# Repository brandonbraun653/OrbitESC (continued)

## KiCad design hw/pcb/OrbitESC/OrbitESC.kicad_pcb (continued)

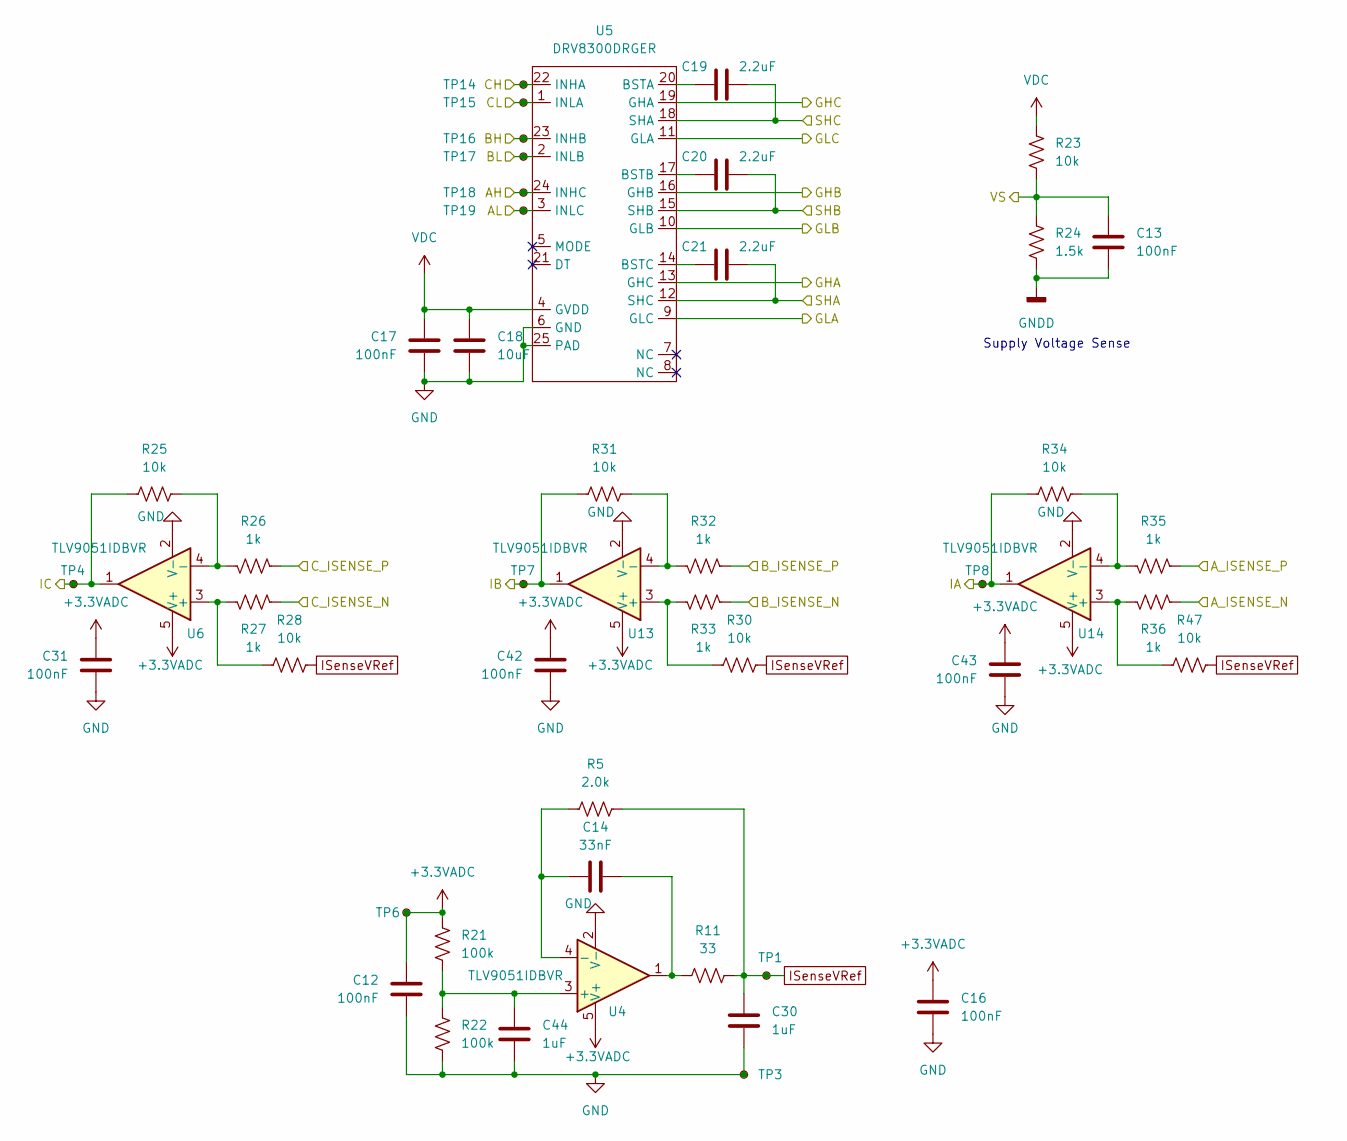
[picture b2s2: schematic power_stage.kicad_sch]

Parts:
C12, C13, C16, C17, C31, C42, C43: 100nF; C_0402_1005Metric; LCSC C307331
C14: 33nF; C_0402_1005Metric; LCSC C1585
C18: 10uF; C_0805_2012Metric; LCSC C440198
C19, C20, C21: 2.2uF; C_0805_2012Metric; LCSC C49217
C30, C44: 1uF; C_0402_1005Metric; LCSC C52923
R5: 2.0k; R_0402_1005Metric; LCSC C4109
R11: 33; R_0402_1005Metric; LCSC C25105
R21, R22: 100k; R_0402_1005Metric; LCSC C25741
R23, R25, R28, R30, R31, R34, R47: 10k; R_0402_1005Metric; LCSC C25744
R24: 1.5k; R_0402_1005Metric; LCSC C25867
R26, R27, R32, R33, R35, R36: 1k; R_0402_1005Metric; LCSC C11702
TP1, TP3, TP17: BL; TestPoint_Pad_D1.0mm
TP4, TP6, TP7, TP8, TP14: AH; TestPoint_Pad_D1.0mm
TP15: AL; TestPoint_Pad_D1.0mm
TP16: BH; TestPoint_Pad_D1.0mm
TP18: CH; TestPoint_Pad_D1.0mm
TP19: CL; TestPoint_Pad_D1.0mm
U4, U6, U13, U14: TLV9051IDBVR; SOT-23-5; LCSC C1849429
U5: DRV8300DRGER; VQFN-24-1EP_4x4mm_P0.5mm_EP2.45x2.45mm; DigiKey 296-DRV8300DRGERCT-ND

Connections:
+3.3VADC: C12.2, C16.1, C31.1, C42.1, C43.1, R21.2, TP6.1, U4.5 (V+), U6.5 (V+), U13.5 (V+), U14.5 (V+); also elsewhere on the board
/MCU/GATE_DRIVE_AH: TP18.1, U5.24 (INHC); also elsewhere on the board
/MCU/GATE_DRIVE_AL: TP19.1, U5.3 (INLC); also elsewhere on the board
/MCU/GATE_DRIVE_BH: TP16.1, U5.23 (INHB); also elsewhere on the board
/MCU/GATE_DRIVE_BL: TP17.1, U5.2 (INLB); also elsewhere on the board
/MCU/GATE_DRIVE_CH: TP14.1, U5.22 (INHA); also elsewhere on the board
/MCU/GATE_DRIVE_CL: TP15.1, U5.1 (INLA); also elsewhere on the board
/MCU/INPUT_VOLTAGE: C13.1, R23.1, R24.1; also elsewhere on the board
/MCU/MOTOR_IA: R34.1, TP8.1, U14.1; also elsewhere on the board
/MCU/MOTOR_IB: R31.1, TP7.1, U13.1; also elsewhere on the board
/MCU/MOTOR_IC: R25.1, TP4.1, U6.1; also elsewhere on the board
/Outputs and Shunts/A_ISENSE_P: R35.1; also elsewhere on the board
/Outputs and Shunts/B_ISENSE_P: R32.1; also elsewhere on the board
/Outputs and Shunts/C_ISENSE_P: R26.1; also elsewhere on the board
/Outputs and Shunts/GDH_A: U5.13 (GHC); also elsewhere on the board
/Outputs and Shunts/GDH_B: U5.16 (GHB); also elsewhere on the board
/Outputs and Shunts/GDH_C: U5.19 (GHA); also elsewhere on the board
/Outputs and Shunts/GDL_A: U5.9 (GLC); also elsewhere on the board
/Outputs and Shunts/GDL_B: U5.10 (GLB); also elsewhere on the board
/Outputs and Shunts/GDL_C: U5.11 (GLA); also elsewhere on the board
/Outputs and Shunts/SH_A: C21.2, U5.12 (SHC); also elsewhere on the board
/Outputs and Shunts/SH_B: C20.2, U5.15 (SHB); also elsewhere on the board
/Outputs and Shunts/SH_C: C19.2, U5.18 (SHA); also elsewhere on the board
GND: C12.1, C13.2, C16.2, C17.1, C18.2, C30.2, C31.2, C42.2, C43.2, C44.2, R22.1, R24.2, R27.1, R33.1, R36.1, TP3.1, U4.2 (V-), U5.6 (GND), U5.25 (PAD), U6.2 (V-), U13.2 (V-), U14.2 (V-); also elsewhere on the board
ISenseVRef: C30.1, R5.1, R11.1, R28.2, R30.2, R47.2, TP1.1
unnamed: C14.1, R5.2, U4.4 (-)
unnamed: C14.2, R11.2, U4.1
unnamed: C19.1, U5.20 (BSTA)
unnamed: C20.1, U5.17 (BSTB)
unnamed: C21.1, U5.14 (BSTC)
unnamed: C44.1, R21.1, R22.2, U4.3 (+)
unnamed: R25.2, R26.2, U6.4 (-)
unnamed: R27.2, R28.1, U6.3 (+)
unnamed: R30.1, R33.2, U13.3 (+)
unnamed: R31.2, R32.2, U13.4 (-)
unnamed: R34.2, R35.2, U14.4 (-)
unnamed: R36.2, R47.1, U14.3 (+)
VDC: C17.2, C18.1, R23.2, U5.4 (GVDD); also elsewhere on the board

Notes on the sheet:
Supply Voltage Sense

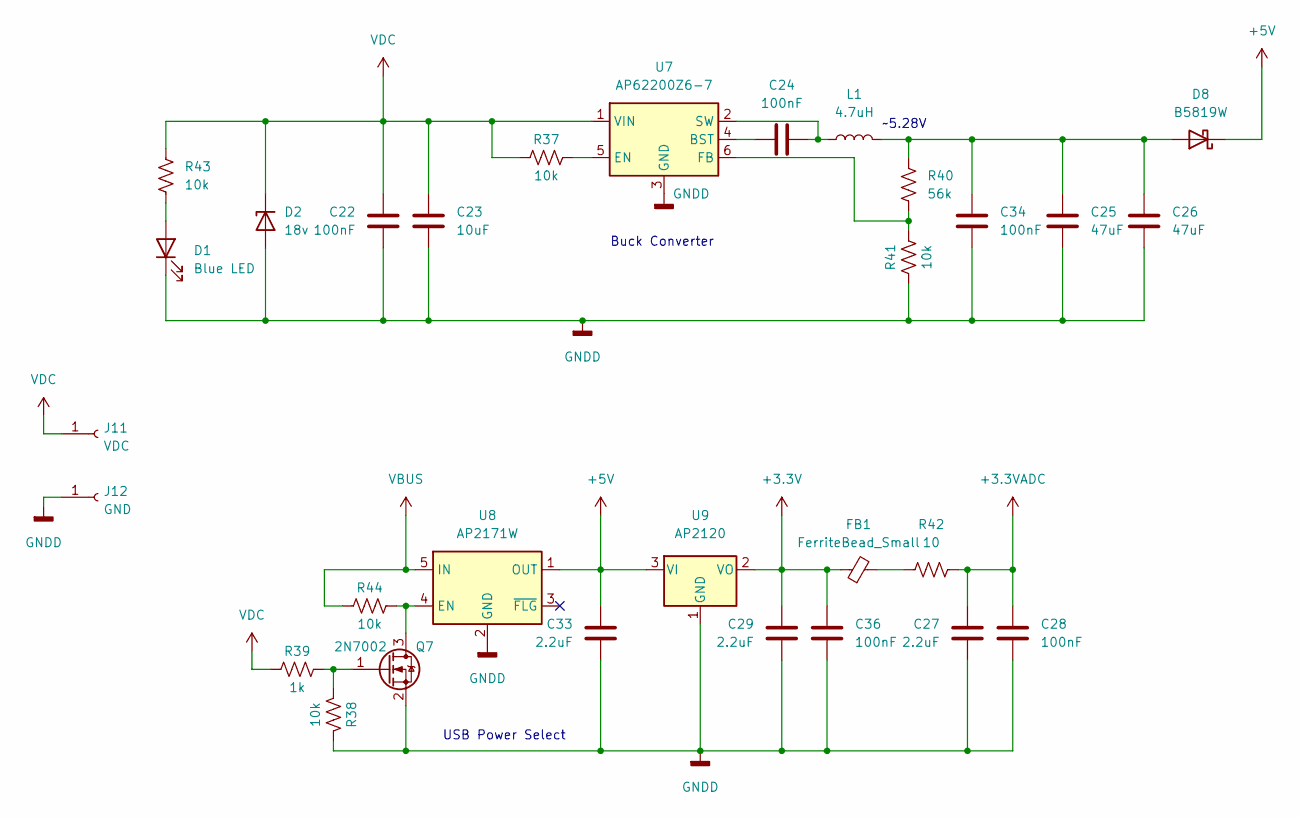
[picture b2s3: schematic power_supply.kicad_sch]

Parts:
C22, C24, C28, C34, C36: 100nF; C_0402_1005Metric; LCSC C307331
C23: 10uF; C_0805_2012Metric; LCSC C440198
C25, C26: 47uF; C_0805_2012Metric; LCSC C16780
C27, C29, C33: 2.2uF; C_0805_2012Metric; LCSC C49217
D1: Blue LED; D_0603_1608Metric; LCSC C72041
D2: 18v; D_SMA; DigiKey SMAZ18-FDICT-ND
D8: B5819W; D_SOD-123; LCSC C8598
FB1: FerriteBead_Small; R_0603_1608Metric; LCSC C1002
J11: VDC; TestPoint_Pad_4.0x4.0mm; DigiKey N/A
J12: GND; TestPoint_Pad_4.0x4.0mm; DigiKey N/A
L1: 4.7uH; L_Bourns-SRN6028; DigiKey 587-2100-1-ND
Q7: 2N7002; SOT-23; LCSC C8545
R37, R38, R41, R43, R44: 10k; R_0402_1005Metric; LCSC C25744
R39: 1k; R_0402_1005Metric; LCSC C11702
R40: 56k; R_0402_1005Metric; DigiKey RMCF0402FT57K6CT-ND
R42: 10; R_0402_1005Metric; LCSC C25077
U7: AP62200Z6-7; SOT-563; DigiKey 31-AP62200Z6-7CT-ND
U8: AP2171W; SOT-23-5; DigiKey AP2171WGDICT-ND
U9: AP2120; SOT-23; DigiKey AP2120N-3.3TRG1DICT-ND

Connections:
+3.3V: C29.2, C36.1, FB1.1, U9.2 (VO); also elsewhere on the board
+3.3VADC: C27.2, C28.1, R42.2; also elsewhere on the board
+5V: C33.2, D8.1 (K), U8.1 (OUT), U9.3 (VI); also elsewhere on the board
GND: C22.1, C23.2, C25.2, C26.2, C27.1, C28.2, C29.1, C33.1, C34.2, C36.2, D1.1 (K), D2.2 (A), J12.1, Q7.2 (S), R38.1, R41.1, U7.3 (GND), U8.2 (GND), U9.1 (GND); also elsewhere on the board
unnamed: C24.1, L1.1, U7.2 (SW)
unnamed: C24.2, U7.4 (BST)
unnamed: C25.1, C26.1, C34.1, D8.2 (A), L1.2, R40.1
unnamed: D1.2 (A), R43.2
unnamed: FB1.2, R42.1
unnamed: Q7.1 (G), R38.2, R39.2
unnamed: Q7.3 (D), R44.2, U8.4 (EN)
unnamed: R37.2, U7.5 (EN)
unnamed: R40.2, R41.2, U7.6 (FB)
VBUS: R44.1, U8.5 (IN); also elsewhere on the board
VDC: C22.2, C23.1, D2.1 (K), J11.1, R37.1, R39.1, R43.1, U7.1 (VIN); also elsewhere on the board

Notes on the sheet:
~5.28V
Buck Converter
USB Power Select

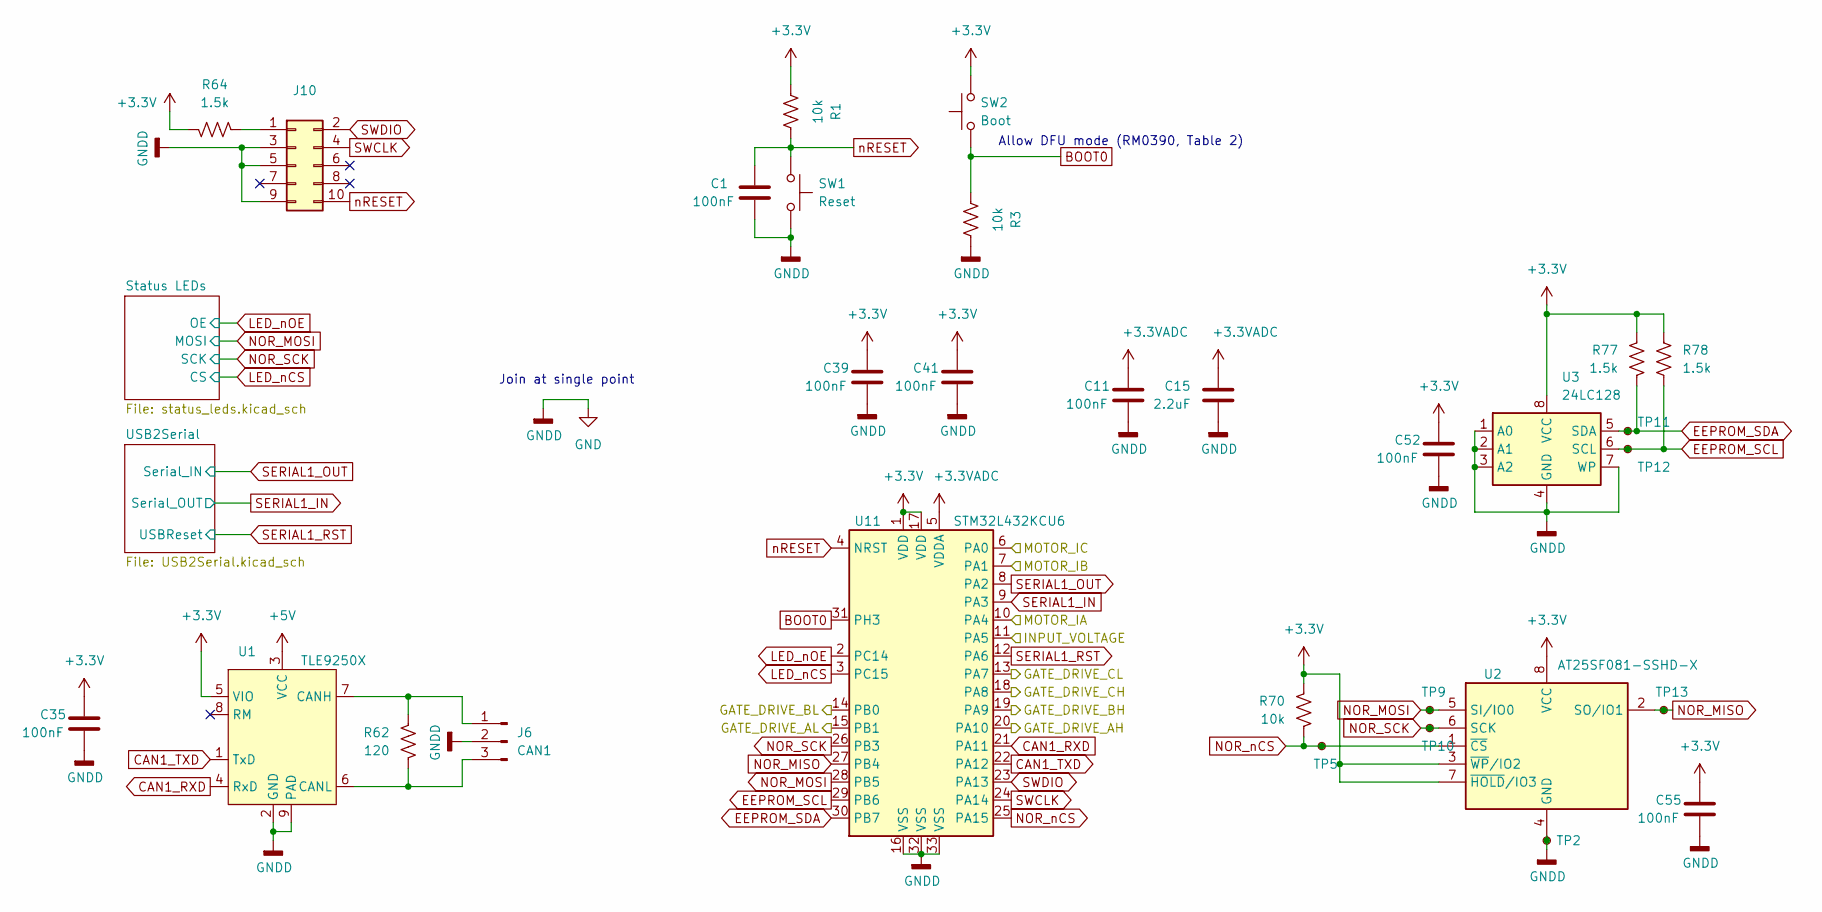
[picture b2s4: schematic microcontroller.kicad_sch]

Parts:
C1, C11, C35, C39, C41, C52, C55: 100nF; C_0402_1005Metric; LCSC C307331
C15: 2.2uF; C_0805_2012Metric; LCSC C49217
J6: CAN1; JST_PH_B3B-PH-K_1x03_P2.00mm_Vertical; DigiKey A100035-ND
J10: PinHeader_2x05_P1.27mm_Vertical; DigiKey 609-3712-ND
R1, R3, R70: 10k; R_0402_1005Metric; LCSC C25744
R62: 120; R_0402_1005Metric; LCSC C25079
R64, R77, R78: 1.5k; R_0402_1005Metric; LCSC C25867
SW1: Reset; SW_SPST_PTS810; DigiKey CKN10502CT-ND
SW2: Boot; SW_SPST_PTS810; DigiKey CKN10502CT-ND
TP2, TP13: NOR_MISO; TestPoint_Pad_D1.0mm
TP5: NOR_nCS; TestPoint_Pad_D1.0mm
TP9: NOR_MOSI; TestPoint_Pad_D1.0mm
TP10: NOR_SCK; TestPoint_Pad_D1.0mm
TP11: EEPROM_SDA; TestPoint_Pad_D1.0mm
TP12: EEPROM_SCL; TestPoint_Pad_D1.0mm
U1: TLE9250X; HVSON-8-1EP_3x3mm_P0.65mm_EP1.6x2.4mm; DigiKey 448-TLE9250XLEXUMA1CT-ND
U2: AT25SF081-SSHD-X; SOIC-8_3.9x4.9mm_P1.27mm; DigiKey 1265-AT25SF081B-SSHD-B-ND
U3: 24LC128; MSOP-8_3x3mm_P0.65mm; DigiKey 24LC128T-E/MSCT-ND
U11: STM32L432KCU6; QFN-32-1EP_5x5mm_P0.5mm_EP3.45x3.45mm; LCSC C1337280

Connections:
+3.3V: C35.2, C39.2, C41.2, C52.2, C55.2, R1.2, R64.2, R70.2, R77.2, R78.1, SW2.2, U1.5 (VIO), U2.3 (~WP/IO2), U2.7 (~HOLD/IO3), U2.8 (VCC), U3.8 (VCC), U11.1 (VDD), U11.17 (VDD); also elsewhere on the board
+3.3VADC: C11.2, C15.2, U11.5 (VDDA); also elsewhere on the board
+5V: U1.3 (VCC); also elsewhere on the board
/MCU/GATE_DRIVE_AH: U11.20 (PA10); also elsewhere on the board
/MCU/GATE_DRIVE_AL: U11.15 (PB1); also elsewhere on the board
/MCU/GATE_DRIVE_BH: U11.19 (PA9); also elsewhere on the board
/MCU/GATE_DRIVE_BL: U11.14 (PB0); also elsewhere on the board
/MCU/GATE_DRIVE_CH: U11.18 (PA8); also elsewhere on the board
/MCU/GATE_DRIVE_CL: U11.13 (PA7); also elsewhere on the board
/MCU/INPUT_VOLTAGE: U11.11 (PA5); also elsewhere on the board
/MCU/MOTOR_IA: U11.10 (PA4); also elsewhere on the board
/MCU/MOTOR_IB: U11.7 (PA1); also elsewhere on the board
/MCU/MOTOR_IC: U11.6 (PA0); also elsewhere on the board
BOOT0: R3.2, SW2.1, U11.31 (PH3)
CAN1_RXD: U1.4 (RxD), U11.21 (PA11)
CAN1_TXD: U1.1 (TxD), U11.22 (PA12)
EEPROM_SCL: R78.2, TP12.1, U3.6 (SCL), U11.29 (PB6)
EEPROM_SDA: R77.1, TP11.1, U3.5 (SDA), U11.30 (PB7)
GND: C1.1, C11.1, C15.1, C35.1, C39.1, C41.1, C52.1, C55.1, J6.2, J10.3, J10.5, J10.9, R3.1, SW1.2, TP2.1, U1.2 (GND), U1.9 (PAD), U2.4 (GND), U3.1 (A0), U3.2 (A1), U3.3 (A2), U3.4 (GND), U3.7 (WP), U11.16 (VSS), U11.32 (VSS), U11.33 (VSS); also elsewhere on the board
LED_nCS: U11.3 (PC15); also elsewhere on the board
LED_nOE: U11.2 (PC14); also elsewhere on the board
NOR_MISO: TP13.1, U2.2 (SO/IO1), U11.27 (PB4)
NOR_MOSI: TP9.1, U2.5 (SI/IO0), U11.28 (PB5); also elsewhere on the board
NOR_SCK: TP10.1, U2.6 (SCK), U11.26 (PB3); also elsewhere on the board
NOR_nCS: R70.1, TP5.1, U2.1 (~CS), U11.25 (PA15)
unnamed: J6.1, R62.2, U1.7 (CANH)
unnamed: J6.3, R62.1, U1.6 (CANL)
unnamed: J10.1, R64.1
SERIAL1_IN: U11.9 (PA3); also elsewhere on the board
SERIAL1_OUT: U11.8 (PA2); also elsewhere on the board
SERIAL1_RST: U11.12 (PA6); also elsewhere on the board
SWCLK: J10.4, U11.24 (PA14)
SWDIO: J10.2, U11.23 (PA13)
nRESET: C1.2, J10.10, R1.1, SW1.1, U11.4 (NRST)

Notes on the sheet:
Join at single point
Allow DFU mode (RM0390, Table 2)

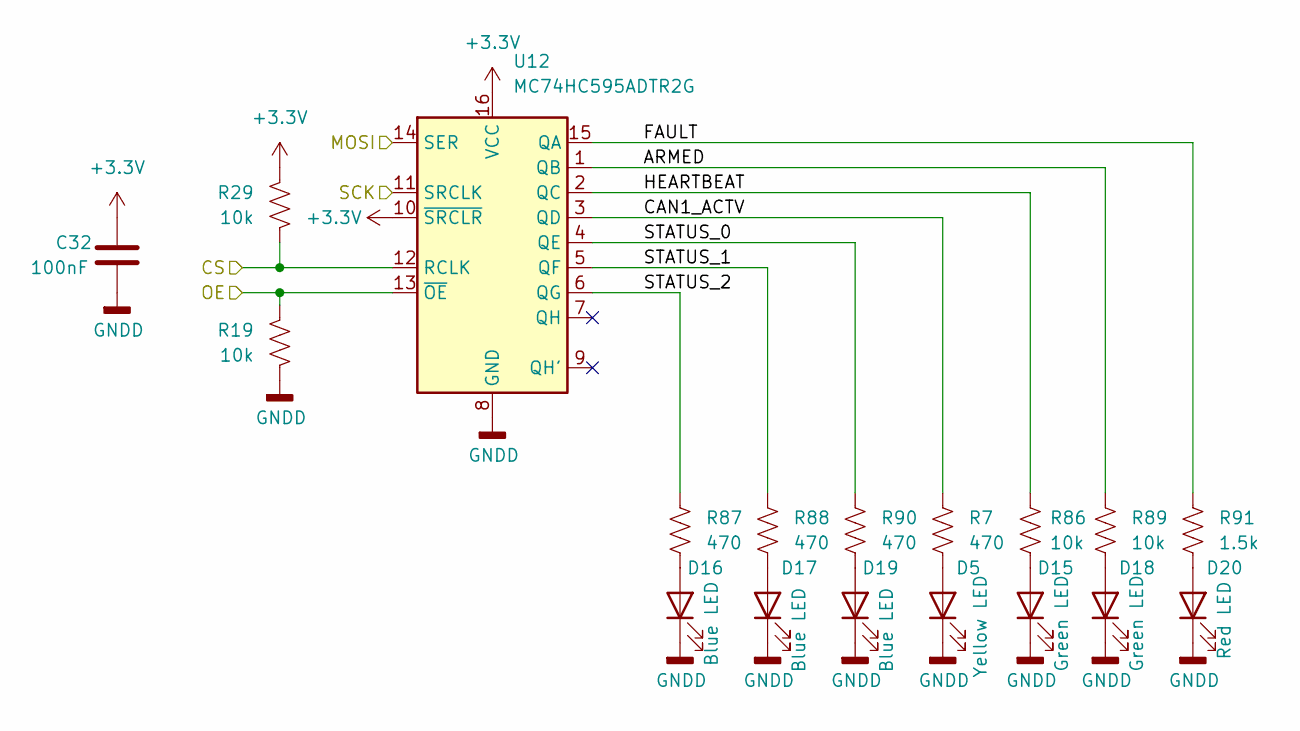
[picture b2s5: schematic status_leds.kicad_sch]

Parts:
C32: 100nF; C_0402_1005Metric; LCSC C307331
D5: Yellow LED; D_0603_1608Metric; LCSC C72038
D15, D18: Green LED; D_0603_1608Metric; LCSC C72043
D16, D17, D19: Blue LED; D_0603_1608Metric; LCSC C72041
D20: Red LED; D_0603_1608Metric; LCSC C2286
R7, R87, R88, R90: 470; R_0402_1005Metric; LCSC C25117
R19, R29, R86, R89: 10k; R_0402_1005Metric; LCSC C25744
R91: 1.5k; R_0402_1005Metric; LCSC C25867
U12: MC74HC595ADTR2G; TSSOP-16_4.4x5mm_P0.65mm; LCSC C100027

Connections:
+3.3V: C32.2, R29.2, U12.10 (~SRCLR), U12.16 (VCC); also elsewhere on the board
/MCU/Status LEDs/ARMED: R89.1, U12.1 (QB)
/MCU/Status LEDs/CAN1_ACTV: R7.1, U12.3 (QD)
/MCU/Status LEDs/FAULT: R91.1, U12.15 (QA)
/MCU/Status LEDs/HEARTBEAT: R86.1, U12.2 (QC)
/MCU/Status LEDs/STATUS_0: R90.1, U12.4 (QE)
/MCU/Status LEDs/STATUS_1: R88.1, U12.5 (QF)
/MCU/Status LEDs/STATUS_2: R87.1, U12.6 (QG)
GND: C32.1, D5.1 (K), D15.1 (K), D16.1 (K), D17.1 (K), D18.1 (K), D19.1 (K), D20.1 (K), R19.1, U12.8 (GND); also elsewhere on the board
LED_nCS: R29.1, U12.12 (RCLK); also elsewhere on the board
LED_nOE: R19.2, U12.13 (~OE); also elsewhere on the board
NOR_MOSI: U12.14 (SER); also elsewhere on the board
NOR_SCK: U12.11 (SRCLK); also elsewhere on the board
unnamed: D5.2 (A), R7.2
unnamed: D15.2 (A), R86.2
unnamed: D16.2 (A), R87.2
unnamed: D17.2 (A), R88.2
unnamed: D18.2 (A), R89.2
unnamed: D19.2 (A), R90.2
unnamed: D20.2 (A), R91.2

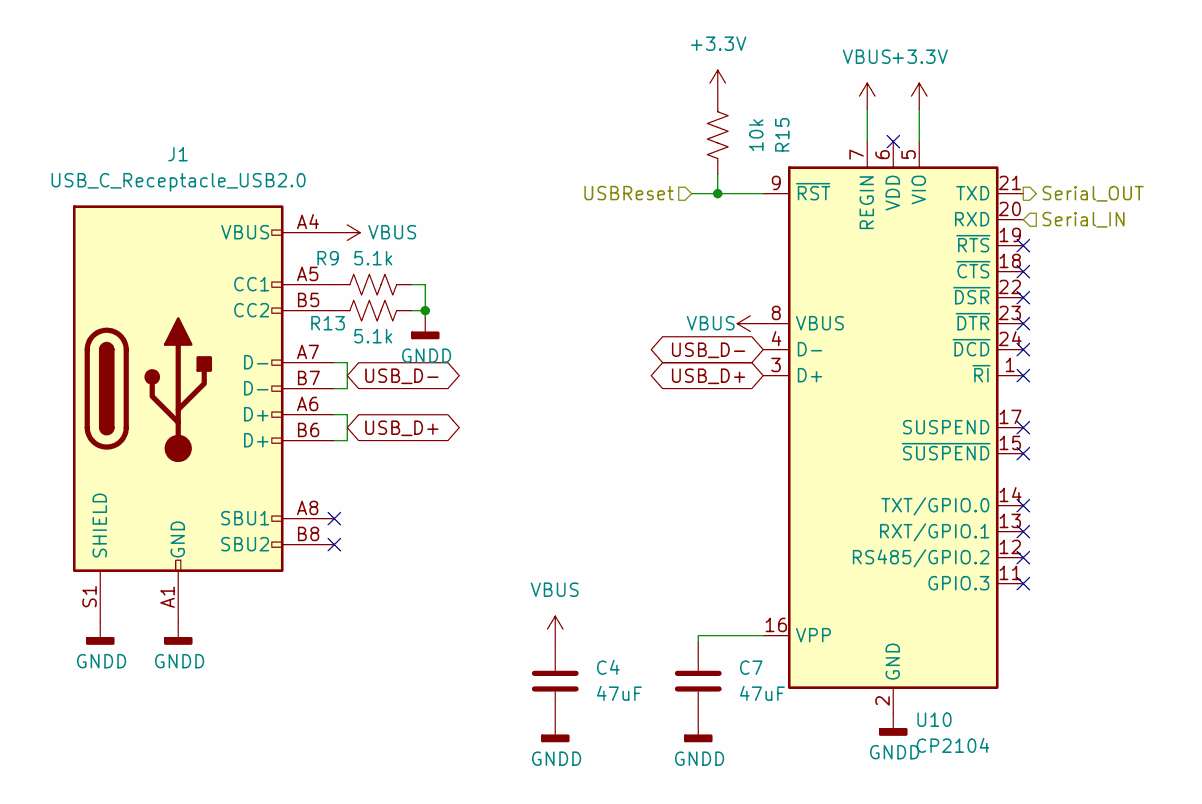
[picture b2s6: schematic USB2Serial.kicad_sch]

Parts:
C4, C7: 47uF; C_0805_2012Metric; LCSC C16780
J1: USB_C_Receptacle_USB2.0; USB_C_Receptacle_GCT_USB4085
R9, R13: 5.1k; R_0402_1005Metric; LCSC C25905
R15: 10k; R_0402_1005Metric; LCSC C25744
U10: CP2104; QFN-24-1EP_4x4mm_P0.5mm_EP2.6x2.6mm

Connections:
+3.3V: R15.2, U10.5 (VIO); also elsewhere on the board
GND: C4.2, C7.2, J1.A1 (GND), J1.A12 (GND), J1.B1 (GND), J1.B12 (GND), J1.S1 (SHIELD), R9.1, R13.2, U10.2 (GND), U10.25 (GND); also elsewhere on the board
unnamed: C7.1, U10.16 (VPP)
unnamed: J1.A5 (CC1), R9.2
unnamed: J1.B5 (CC2), R13.1
SERIAL1_IN: U10.21 (TXD); also elsewhere on the board
SERIAL1_OUT: U10.20 (RXD); also elsewhere on the board
SERIAL1_RST: R15.1, U10.9 (~RST); also elsewhere on the board
USB_D+: J1.A6 (D+), J1.B6 (D+), U10.3 (D+)
USB_D-: J1.A7 (D-), J1.B7 (D-), U10.4 (D-)
VBUS: C4.1, J1.A4 (VBUS), J1.A9 (VBUS), J1.B4 (VBUS), J1.B9 (VBUS), U10.7 (REGIN), U10.8 (VBUS); also elsewhere on the board

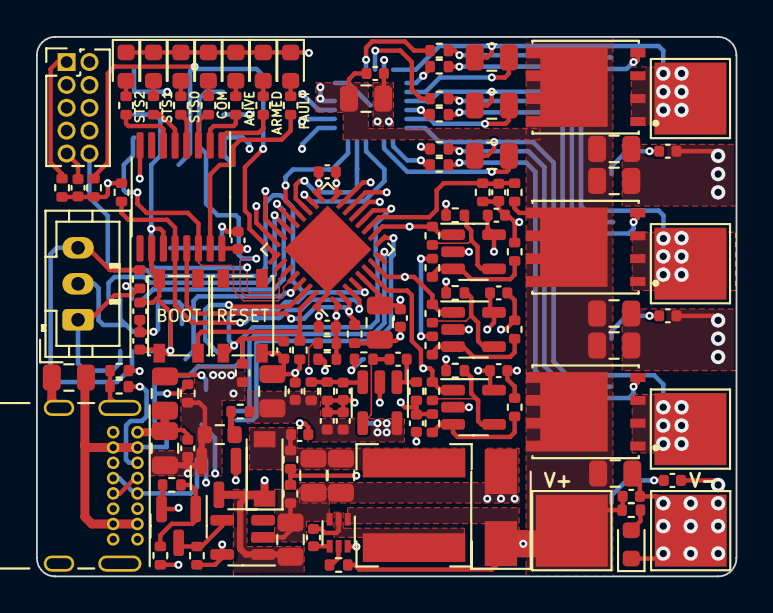
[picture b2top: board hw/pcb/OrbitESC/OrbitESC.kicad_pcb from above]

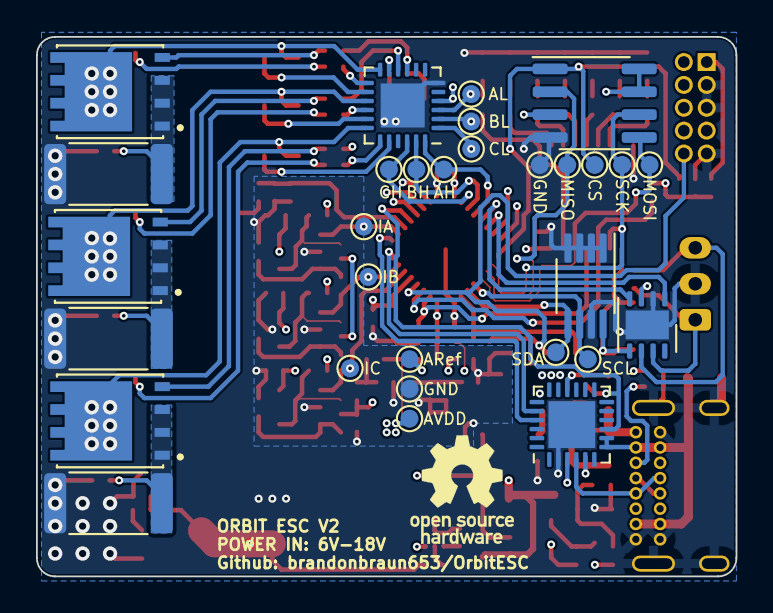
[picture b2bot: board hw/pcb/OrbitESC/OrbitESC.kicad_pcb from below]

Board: 4 copper layers, 38.9 x 30.0 mm, 159 parts (30 on the bottom side), 95 nets.

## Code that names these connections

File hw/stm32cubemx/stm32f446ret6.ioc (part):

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Mcu.Name=STM32F446R(C-E)Tx
Mcu.Package=LQFP64
Mcu.UserName=STM32F446RETx
PA0-WKUP.Signal=ADCx_IN0
PA1.Signal=ADCx_IN1
PA10.Signal=S_TIM1_CH3
PA11.Mode=CAN_Activate
PA11.Signal=CAN1_RX
PA12.Mode=CAN_Activate
PA12.Signal=CAN1_TX
PA13.Mode=Serial_Wire
PA13.Signal=SYS_JTMS-SWDIO
PA14.Mode=Serial_Wire
PA14.Signal=SYS_JTCK-SWCLK
PA15.Mode=NSS_Signal_Hard_Output
PA15.Signal=SPI1_NSS
PA2.Signal=ADCx_IN2
PA3.Signal=ADCx_IN3
PA4.Signal=ADCx_IN4
PA5.Signal=ADCx_IN5
PA7.Mode=Output Compare1 CH1 CH1N
PA7.Signal=TIM1_CH1N
PA8.Signal=S_TIM1_CH1
PA9.Signal=S_TIM1_CH2
PB0.Mode=Output Compare2 CH2 CH2N
PB0.Signal=TIM1_CH2N
PB1.Mode=Output Compare3 CH3 CH3N
PB1.Signal=TIM1_CH3N
PB10.GPIOParameters=GPIO_Label
PB10.GPIO_Label=SDIO_DET
PB10.Signal=GPIO_Input
PB12.GPIOParameters=GPIO_Label
PB12.GPIO_Label=USB_OTG_HS_RESET
PB12.Signal=GPIO_Output
PB13.Mode=Activate_VBUS_FS
PB13.Signal=USB_OTG_HS_VBUS
PB14.Mode=Device_Only_FS
PB14.Signal=USB_OTG_HS_DM
PB15.Mode=Device_Only_FS
PB15.Signal=USB_OTG_HS_DP
PB3.Mode=Full_Duplex_Master
PB3.Signal=SPI1_SCK
PB4.Mode=Full_Duplex_Master
PB4.Signal=SPI1_MISO
PB5.Mode=Full_Duplex_Master
PB5.Signal=SPI1_MOSI
PB6.GPIOParameters=GPIO_Label
PB6.GPIO_Label=Fault
PB6.Signal=GPIO_Output
PB7.GPIOParameters=GPIO_Label
PB7.GPIO_Label=Armed
PB7.Signal=GPIO_Output
PB8.GPIOParameters=GPIO_Label
PB8.GPIO_Label=Heartbeat
PB8.Signal=GPIO_Output
PB9.GPIOParameters=GPIO_Label
PB9.GPIO_Label=CAN Activity
PB9.Signal=GPIO_Output
PC0.Signal=ADCx_IN10
PC1.Signal=ADCx_IN11
PC10.Mode=SD_4_bits_Wide_bus
PC10.Signal=SDIO_D2
PC11.Mode=SD_4_bits_Wide_bus
PC11.Signal=SDIO_D3
PC12.Mode=SD_4_bits_Wide_bus
PC12.Signal=SDIO_CK
PC13.GPIOParameters=GPIO_Label
PC13.GPIO_Label=USB Activity
PC13.Signal=GPIO_Output
PC2.Signal=ADCx_IN12
PC3.Signal=ADCx_IN13
PC6.Mode=Asynchronous
PC6.Signal=USART6_TX
PC7.Mode=Asynchronous
PC7.Signal=USART6_RX
PC8.Mode=SD_4_bits_Wide_bus
PC8.Signal=SDIO_D0
PC9.Mode=SD_4_bits_Wide_bus
PC9.Signal=SDIO_D1
PD2.Mode=SD_4_bits_Wide_bus
PD2.Signal=SDIO_CMD
PH0-OSC_IN.Mode=HSE-External-Oscillator
PH0-OSC_IN.Signal=RCC_OSC_IN
PH1-OSC_OUT.Mode=HSE-External-Oscillator
PH1-OSC_OUT.Signal=RCC_OSC_OUT
RCC.HSE_VALUE=24000000
RCC.SYSCLKFreq_VALUE=180000000
RCC.SYSCLKSource=RCC_SYSCLKSOURCE_PLLCLK
board=custom

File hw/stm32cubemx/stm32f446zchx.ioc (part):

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Mcu.Name=STM32F446Z(C-E)Hx
Mcu.Package=UFBGA144
Mcu.UserName=STM32F446ZCHx
PA0-WKUP.GPIOParameters=GPIO_Label
PA0-WKUP.GPIO_Label=INPUT_VOLTAGE
PA0-WKUP.Signal=ADCx_IN0
PA1.GPIOParameters=GPIO_Label
PA1.GPIO_Label=MOTOR_IA
PA1.Signal=ADCx_IN1
PA10.GPIOParameters=GPIO_Label
PA10.GPIO_Label=USB COM LED
PA10.Signal=GPIO_Output
PA11.Mode=Device_Only
PA11.Signal=USB_OTG_FS_DM
PA12.Mode=Device_Only
PA12.Signal=USB_OTG_FS_DP
PA13.Mode=JTAG_5_pins
PA13.Signal=SYS_JTMS-SWDIO
PA14.Mode=JTAG_5_pins
PA14.Signal=SYS_JTCK-SWCLK
PA15.Mode=JTAG_5_pins
PA15.Signal=SYS_JTDI
PA2.GPIOParameters=GPIO_Label
PA2.GPIO_Label=MOTOR_IB
PA2.Signal=ADCx_IN2
PA3.GPIOParameters=GPIO_Label
PA3.GPIO_Label=MOTOR_IC
PA3.Signal=ADCx_IN3
PA4.GPIOParameters=GPIO_Label
PA4.GPIO_Label=MOTOR_VA
PA4.Signal=ADCx_IN4
PA5.GPIOParameters=GPIO_Label
PA5.GPIO_Label=MOTOR_VB
PA5.Signal=ADCx_IN5
PA6.GPIOParameters=GPIO_Label
PA6.GPIO_Label=MOTOR_VC
PA6.Signal=ADCx_IN6
PA8.GPIOParameters=GPIO_Label
PA8.GPIO_Label=USB Renumerate
PA8.Signal=GPIO_Output
PA9.Mode=Activate_VBUS
PA9.Signal=USB_OTG_FS_VBUS
PB12.GPIOParameters=GPIO_Label
PB12.GPIO_Label=SPI CS
PB12.Signal=GPIO_Output
PB13.Mode=Full_Duplex_Master
PB13.Signal=SPI2_SCK
PB14.Mode=Full_Duplex_Master
PB14.Signal=SPI2_MISO
PB15.Mode=Full_Duplex_Master
PB15.Signal=SPI2_MOSI
PB2.GPIOParameters=GPIO_Label
PB2.GPIO_Label=BOOT
PB2.Signal=GPIO_Input
PB3.Mode=JTAG_5_pins
PB3.Signal=SYS_JTDO-SWO
PB4.Mode=JTAG_5_pins
PB4.Signal=SYS_JTRST
PB5.Mode=CAN_Activate
PB5.Signal=CAN2_RX
PB6.Mode=CAN_Activate
PB6.Signal=CAN2_TX
PB8.Mode=CAN_Activate
PB8.Signal=CAN1_RX
PB9.Mode=CAN_Activate
PB9.Signal=CAN1_TX
PC0.GPIOParameters=GPIO_Label
PC0.GPIO_Label=SUPPLY_5V0
PC0.Signal=ADCx_IN10
PC10.Mode=SD_4_bits_Wide_bus
PC10.Signal=SDIO_D2
PC11.Mode=SD_4_bits_Wide_bus
PC11.Signal=SDIO_D3
PC12.Mode=SD_4_bits_Wide_bus
PC12.Signal=SDIO_CK
PC13.GPIOParameters=GPIO_Label
PC13.GPIO_Label=HEARTBEAT LED
PC13.Signal=GPIO_Output
PC8.Mode=SD_4_bits_Wide_bus
PC8.Signal=SDIO_D0
PC9.Mode=SD_4_bits_Wide_bus
PC9.Signal=SDIO_D1
PD1.GPIOParameters=GPIO_Label
PD1.GPIO_Label=SDIO_CARD_DETECT
PD1.Signal=GPXTI1
PD2.Mode=SD_4_bits_Wide_bus
PD2.Signal=SDIO_CMD
PD5.Mode=Asynchronous
PD5.Signal=USART2_TX
PD6.Mode=Asynchronous
PD6.Signal=USART2_RX
PE0.GPIOParameters=GPIO_Label
PE0.GPIO_Label=CAN1 COM LED
PE0.Signal=GPIO_Output
PE1.GPIOParameters=GPIO_Label
PE1.GPIO_Label=MOTOR_ARMED
PE1.Signal=GPIO_Output
PE10.Mode=Output Compare2 CH2 CH2N
PE10.Signal=TIM1_CH2N
PE11.Signal=S_TIM1_CH2
PE12.Mode=Output Compare3 CH3 CH3N
PE12.Signal=TIM1_CH3N
PE13.Signal=S_TIM1_CH3
PE15.GPIOParameters=GPIO_Label
PE15.GPIO_Label=BREAK
PE15.Mode=Activate-Break-Input
PE15.Signal=TIM1_BKIN
PE2.GPIOParameters=GPIO_Label
PE2.GPIO_Label=MOTOR_FAULT
PE2.Signal=GPIO_Output
PE3.GPIOParameters=GPIO_Label
PE3.GPIO_Label=USER_BTN
PE3.Signal=GPIO_Input
PE4.GPIOParameters=GPIO_Label
PE4.GPIO_Label=STATUS_0_LED
PE4.Signal=GPIO_Output
PE5.GPIOParameters=GPIO_Label
PE5.GPIO_Label=STATUS_1_LED
PE5.Signal=GPIO_Output
PE6.GPIOParameters=GPIO_Label
PE6.GPIO_Label=STATUS_2_LED
PE6.Signal=GPIO_Output
PE8.Mode=Output Compare1 CH1 CH1N
PE8.Signal=TIM1_CH1N
PE9.Signal=S_TIM1_CH1
PF0.Mode=I2C
PF0.Signal=I2C2_SDA
PF1.Mode=I2C
PF1.Signal=I2C2_SCL
PF10.GPIOParameters=GPIO_Label
PF10.GPIO_Label=SUPPLY_3V3
PF10.Mode=IN8
PF10.Signal=ADC3_IN8
PF3.GPIOParameters=GPIO_Label
PF3.GPIO_Label=BOARD_TEMP_A
PF3.Mode=IN9
PF3.Signal=ADC3_IN9
PF9.GPIOParameters=GPIO_Label
PF9.GPIO_Label=BOARD_TEMP_B
PF9.Mode=IN7
PF9.Signal=ADC3_IN7
PG12.GPIOParameters=GPIO_Label
PG12.GPIO_Label=SERIAL1_COM_LED
PG12.Signal=GPIO_Output
PG13.GPIOParameters=GPIO_Label
PG13.GPIO_Label=SERIAL2_COM_LED
PG13.Signal=GPIO_Output
PG14.Mode=Asynchronous
PG14.Signal=USART6_TX
PG15.GPIOParameters=GPIO_Label
PG15.GPIO_Label=CAN2 COM LED
PG15.Signal=GPIO_Output
PG9.Mode=Asynchronous
PG9.Signal=USART6_RX
PH0-OSC_IN.Mode=HSE-External-Oscillator
PH0-OSC_IN.Signal=RCC_OSC_IN
PH1-OSC_OUT.Mode=HSE-External-Oscillator
PH1-OSC_OUT.Signal=RCC_OSC_OUT
RCC.HSE_VALUE=24000000
RCC.SYSCLKFreq_VALUE=180000000
RCC.SYSCLKSource=RCC_SYSCLKSOURCE_PLLCLK
board=custom

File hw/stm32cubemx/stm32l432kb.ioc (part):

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Mcu.Name=STM32L432K(B-C)Ux
Mcu.Package=UFQFPN32
Mcu.UserName=STM32L432KBUx
PA0.Signal=ADCx_IN5
PA1.Signal=ADCx_IN6
PA10.Signal=S_TIM1_CH3
PA11.Mode=CAN_Activate
PA11.Signal=CAN1_RX
PA12.Mode=CAN_Activate
PA12.Signal=CAN1_TX
PA13\ (JTMS-SWDIO).Signal=SYS_JTMS-SWDIO
PA14\ (JTCK-SWCLK).Signal=SYS_JTCK-SWCLK
PA15\ (JTDI).GPIOParameters=GPIO_Label
PA15\ (JTDI).GPIO_Label=NOR_nCS
PA15\ (JTDI).Signal=GPIO_Output
PA2.Signal=ADCx_IN7
PA3.Signal=ADCx_IN8
PA4.Signal=ADCx_IN9
PA5.Signal=ADCx_IN10
PA6.Signal=ADCx_IN11
PA7.Mode=PWM Generation1 CH1 CH1N
PA7.Signal=TIM1_CH1N
PA8.Signal=S_TIM1_CH1
PA9.Signal=S_TIM1_CH2
PB0.Mode=PWM Generation2 CH2 CH2N
PB0.Signal=TIM1_CH2N
PB1.Mode=PWM Generation3 CH3 CH3N
PB1.Signal=TIM1_CH3N
PB3\ (JTDO-TRACESWO).Mode=Full_Duplex_Master
PB3\ (JTDO-TRACESWO).Signal=SPI3_SCK
PB4\ (NJTRST).Mode=Full_Duplex_Master
PB4\ (NJTRST).Signal=SPI3_MISO
PB5.Mode=Full_Duplex_Master
PB5.Signal=SPI3_MOSI
PB6.Mode=Asynchronous
PB6.Signal=USART1_TX
PB7.Mode=Asynchronous
PB7.Signal=USART1_RX
PC14-OSC32_IN\ (PC14).GPIOParameters=GPIO_Label
PC14-OSC32_IN\ (PC14).GPIO_Label=LED_nOE
PC14-OSC32_IN\ (PC14).Signal=GPIO_Output
PC15-OSC32_OUT\ (PC15).GPIOParameters=GPIO_Label
PC15-OSC32_OUT\ (PC15).GPIO_Label=LED_nCS
PC15-OSC32_OUT\ (PC15).Signal=GPIO_Output
PH3-BOOT0.GPIOParameters=GPIO_Label
PH3-BOOT0.GPIO_Label=BootMode
PH3-BOOT0.Signal=GPIO_Input
RCC.HSE_VALUE=8000000
RCC.SYSCLKFreq_VALUE=80000000
RCC.SYSCLKSource=RCC_SYSCLKSOURCE_PLLCLK
board=custom

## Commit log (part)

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2022-10-03 Sync some thoughts on how to structure the new ISR update routines
2022-10-16 Save a few board changes found when assembing PCB v1.0
2022-10-17 Save work for lunch efforts tomorrow. EEPROM updates
2022-10-17 Work on containerization
2022-10-17 Fix EEPROM addressing issues
2022-10-20 Clean up toolchain
2022-10-24 Start integration of filesystem
2022-10-26 Add placeholders for logging sinks
2022-10-26 Start adding the logging infrastructure
2022-10-28 Fill out more of the logging subsystem
2022-10-30 Filesystem mounting with no malloc
2022-10-31 Improve NOR driver
2022-11-02 Start adding some of the eeprom readout
2022-11-06 Attempts to figure out why LittleFS isn't working
2022-11-07 Get the simulator target compiling
2022-11-09 Update sim repo
2022-11-10 Try out filesystem with simulator
2022-11-11 Try out the hw build. FS doesn't seem to work.
2022-11-14 Sync for work
2022-11-16 Found bug, save work
2022-11-18 Little bit of project cleanup
2022-11-21 Start adding the system analog monitors
2022-11-24 Publish phase C current measurements
2022-11-25 Start adding simulation for analog
2022-11-26 Start integration of protocol buffers for serial command and control
2022-11-28 Add basic outline of inner control loop
2022-11-28 Schematic corrections
2022-11-29 Sync PCB updates
2022-11-30 Sync work
2022-12-01 Sync today's work
2022-12-03 Route analogs and starting power stage
2022-12-04 Route power stage of the motor drive
2022-12-06 Add FIR filter algorithm
2022-12-06 Fix some PWM issues
2022-12-08 Start refactoring FOC
2022-12-10 Implement HW analog watchdog monitoring for current and voltage
2022-12-11 Sync work for in-progress serial driver updates
2022-12-12 Increase serial buffer size to print all characters
2022-12-13 Pull up submodules
2022-12-13 Start working on proto interface
2022-12-16 Work on serial driver interface
2022-12-17 Start adding cobs framing
2022-12-20 Update kicad libs
2022-12-21 Sync between pc
2022-12-22 Sync for PC
2023-01-11 Update compiler path. Disable motor drive output enable.
2023-01-13 Sync
2023-01-17 Trying to figure out USART RX
2023-01-18 USART DMA TX working
2023-01-19 Reduce project memory usage
2023-01-22 Ping message working
2023-01-22 Update memory allocations
2023-01-24 Improve framing technique. Fix infinite loop in serial dispatcher.
2023-01-30 Increase debug port baud rate to 2MBit
2023-01-30 Sync work from lunch
2023-02-01 Start added parameter io processing
2023-02-03 Implement full parameter load/store RPC calls
2023-02-03 Parameter GET working
2023-02-05 Add improved support to parameters. Implement read-only tests
2023-02-05 Add system reset command
2023-02-06 Change LED blink rate
2023-02-28 Add mode switching tests
2023-02-28 Save lunchtime work. Change CAN bus activity LED control method.
2023-03-01 Start adding CAN id parameter setting. Freezing somewhere.
2023-03-01 Don't set CAN id to PC in test
2023-03-02 Add parameter validation on save
2023-03-06 Improve parameter storage.
2023-03-07 Add sanity tests for remaining parameters
2023-03-10 Sync some work
2023-03-14 Reorder boot initialization so peripherals can use reconfigurable settings
2023-03-18 Improve adc calibration. Maybe
2023-03-29 Validate my ISRs are firing in the new configuration
2023-03-29 Start planning out basic motor startup
2023-03-30 Sketch out startup equation
2023-03-31 Trying to figure out a decent startup routine
2023-04-11 Try and figure out current sense issues
2023-04-16 Start live plotting motor current to help with debugging ADC settings
2023-04-19 Start work on PCB v3
2023-04-24 Toy around with the driver. Start adding Qt gui
2023-04-24 Cleanup sim directory
2023-05-01 Start adding graphical interface
2023-05-04 Think I improved the current loop controller?
2023-05-06 Dramatically improve look of GUI
2023-05-08 Hurrah! I actually got closed loop current control to semi-work!
2023-05-08 Start adding GUI parameter updater
2023-05-11 Got a single parameter to update through GUI
2023-05-27 Lazy sync for work over the past few weeks. Been busy
2023-06-06 Save some PCB work
2023-06-08 Update SDIO card detect
2023-06-09 Semi-final schematic for F4 variant
2023-06-09 Save tonight's PCB work
2023-06-11 Finish initial draft of V3 pcb
2023-06-13 PCB cleanup. BOM checks.
2023-06-14 Squash feature/sync_current_ctrl/r0
2023-06-21 Update Thor
2023-06-22 Sync before branch for new board mapping
2023-06-25 Clean up a few more interfaces. Discovered NOR isn't working
2023-06-26 More board turn on things
2023-06-27 Fix USART init bug
2023-06-29 Fix NOR flash bootup
2023-08-17 Pull up submodules to include sdio driver support
2023-08-18 Pull up tinyusb to v0.15.0
2023-08-19 Update some submodule pointers.
2023-08-19 Add submodule checkout script
2023-08-20 Sync to PC
2023-08-20 Update history depth
2023-08-20 Start refactoring motor hw driver for timer split
2023-08-22 Slave timer config first attempt. Not great.
2023-08-23 Get both instrumentation and motor sense ADCs firing off timers with DMA
2023-08-26 Get debug pin toggling on ADC output
2023-08-26 Start implementing the motor control loops. Fix timer clocking issue.
2023-08-26 Formalize the debug/release build targets
2023-08-27 Update clocking scheme in MXCube
2023-08-28 Add simple motor ADC DC offset calibration
2023-09-01 Add some filtering, maybe.
2023-09-01 Update simulation
2023-09-03 Got first cut of SVM working on the controller
2023-09-04 Refactor observer methods and state publishing methods
2023-09-07 Sync initial effort to figuring out some current control parameters
2023-09-14 Remove tinyusb as a submodule
2023-09-14 Add back tinyusb from source
2023-09-14 Update the tinyusb config with possibly OK settings
2023-09-16 Remove some unused tinyusb code
2023-09-19 USB is attempting to enumerate. Not quite working yet.
2023-09-21 Remove FlashDB as submodule. Hardcoded config file.
2023-09-21 Add basic compiling of FlashDB + filesystem stubs
2023-09-28 Do a fair amount of refactoring
2023-09-29 Start connecting volatile parameter updates to persistent backing.
2023-09-30 Sync for move to new PC
2023-09-30 FAL init and writes appear to be working
2023-09-30 Finish the database backend refactor
2023-10-02 Start the transition to FatFs support for SD card
2023-10-08 First successful mounting of SD card
2023-10-08 Almost working async SD card mount/unmount
2023-10-10 Improve the file log sink
2023-10-13 Try messing around with increasing SDIO bus throughput
2023-10-16 Investigation into USB driver pt1
2023-10-17 Start work on more thorough segger integration
2023-10-20 Bring segger configuration project side. Start adding modules.
2023-10-24 Debugging descriptor packet transfer
2023-10-26 Swap out to TinyUSB v0.15.0. Change to dwc2 driver.
2023-10-29 USB is working!
2023-10-31 Save some notes from studying the CDC implementation
2023-11-02 Fix buffer overrun issues with CDC stack. Not sure if data is coherent yet.
2023-11-04 Add USB connection status callbacks and initialize module data
2023-11-06 Start adding poetry
2023-11-06 Further improve poetry setup
2023-11-07 Update .gitignore and remove __pycache__ file
2023-11-07 Fix logging and buffer size issues in USART driver
2023-11-12 Add interface to listen for an exact transaction response
2023-11-15 Sync to main pc
2023-11-15 Refactor the PyOrbit communication layer
2023-11-17 Work on improving proto interface
2023-11-19 Flesh out a few scheduler ideas
2023-11-23 Save work
2023-11-27 Improve message scheduling frequency
2023-11-29 Sync for work on PC
2023-11-29 Refactor some of the state transitions.
2023-12-01 Start working on updating protobuf defs
2023-12-01 Further split the proto data
2023-12-03 Get the pyorbit app mostly running again
2023-12-04 Encode sub-payloads with nanobp as well
2023-12-05 Get the Idle->Arm->Idle transitions working
2023-12-06 Add ARMED phase current data streaming test
2023-12-06 Add support for measuring/controlling phase voltage streaming
2023-12-15 Refactor the motor drivers to have a more explicit api
2023-12-23 Add doxygen project
2024-01-17 Clean up warning from arm-none-eabi-gcc v13.2
2024-01-19 Swap over to current threshold. I don't think the driver output is even turning on.
2024-01-21 Get system environment up to date
2024-01-23 Start experimenting with the timer chaining
2024-01-25 Work a bit on IPD. Getting some kind of data, but nothing clear yet.
2024-01-31 Outline the ramp subroutine
2024-02-05 Mess with the controller implementation
2024-02-07 Mess around a bit more with the model
2024-02-09 Start work on a more formalized align/ramp routine
2024-02-11 Fairly decent ramp with a sigmoid function. Not optimal though.
2024-02-22 Current control debug session
2024-02-25 Force streaming of current control monitor data from ISR to help with debugging control loop.
2024-02-26 Sync today's tuning efforts
2024-02-27 Simulator at least compiles
2024-02-28 Simulator actually runs, though it's not fully functional.
2024-02-28 Solved an accidental bug with flushing parameter memory
2024-02-29 Validate simulated serial connection. Fix a few old time bugs.
2024-03-01 Improve environment setup. Fix a few things with ADC conversions.
2024-03-05 Get some simulation data streaming for the motor model.
2024-03-08 Save sim efforts
2024-03-13 Much much much better open loop ramp-up. Need to tune.
2024-03-31 Sync some ideas from messing around
2024-04-03 Sync some toying around with dynamically generating live plots. Still not detecting closure though.
2024-04-04 Sync lunch ideas to main PC
2024-04-09 Sync back to main pc
2024-04-09 Improved the data streaming speeds for usb
2024-04-09 More messing around
2024-04-10 Learned CMSIS has a DSP library!
2024-04-12 Mess around before work with some simulation
2024-04-15 Lunchtime filter design experimentation
2024-04-20 Improve filter design iteration support. Still not getting good estimator output though.
2024-04-22 Try out the position derivative and filtering models
2024-04-23 Oh no way the observer actually works?! Ladies and gentlement for the first time I predicted the real rotational rate!
2024-04-25 Fix some issues with time accouting in ramp up. Not cleanly transitioning to closed loop control at all.
2025-10-04 Add UV and GCC toolchain installers.
2025-10-04 Improve python linter behavior
2025-10-04 Fix clangd based intellisense
2025-10-04 Update protobuf build pipeline
2025-10-08 Remove env_setup.sh script and update Python version requirements in pyproject.toml to require Python 3.11. Adjust dependencies and build system configuration to use Hatch instead of setuptools. Add 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
2025-10-08 Reduce simulator cpu usage
2025-10-08 Update .gitignore, remove unused Python scripts, and optimize task scheduling in the simulator
2025-10-09 Minor changes for simulink model.
2025-10-09 Add prototype trace interface (NEEDS REVIEW)
2025-10-10 Add C/C++ code snippets for VSCode, refactor trace module, and implement MATLAB simulation callbacks
2025-10-13 Get more complext parameter communication working between Matlab and the Simulator
2025-10-15 Start working on timer integrations
2025-10-20 Pull up submodule
2025-10-22 Actually get the sim to build now.
2025-10-22 Clean up matlab integration with new timer behavior
2025-10-23 Get software controller in the loop with matlab sim data
2025-10-23 Improve motor simulation. Sort of replicate some motor ramp graphs I observed in HW testing.
2025-10-24 Realized my control loop is all wrong for ramping. Need to update.
2025-11-08 Figure out a few more things with PID control stability
2025-11-29 Actually save the parameter generation script
2025-12-07 Start adding structure for cross-axis decoupling
2025-12-13 Add cross-axis decoupling and back-emf decoupling
2025-12-13 Add a reference SMO implementation and Obsidian notebook
2025-12-13 Update .gitignore to ignore all workspace.json files in Obsidian directories
2025-12-14 Start refactoring for the open/close loop transition
2025-12-27 CLOSED LOOP SPEED CONTROL IS WORKING
2026-01-01 Figure out source of ramp theta ref error
2026-01-18 Improve motor control current loop bandwidth restrictions
2026-01-31 Work through some more closed loop control debugging
